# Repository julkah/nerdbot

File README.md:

# Bohlebots Nerdbot

This repository contains the last version of all files of the Nerdbot, a robot build in school with the team "Bohlebots" (bohlebots.de). It was built to participate at Robocup tournament in the 2v2 Soccer Open League. A documentation is enclosed as .pdf in German.

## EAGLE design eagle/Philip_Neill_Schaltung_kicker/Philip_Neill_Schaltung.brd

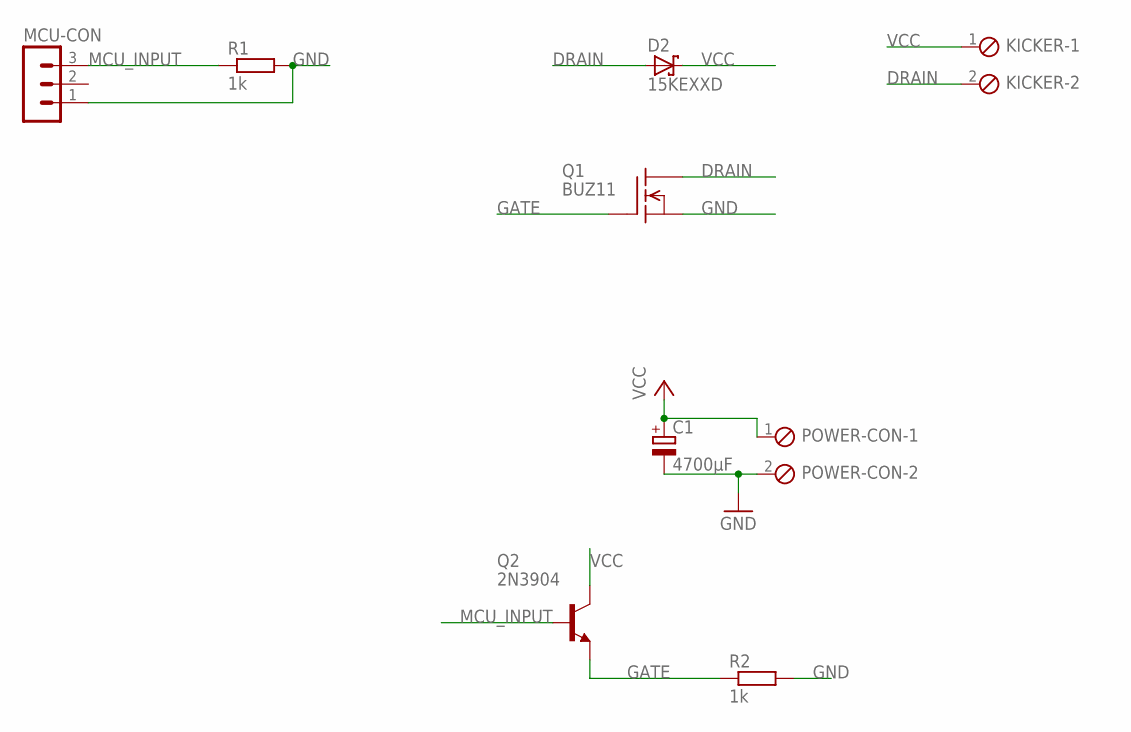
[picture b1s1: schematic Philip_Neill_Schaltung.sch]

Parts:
C1: 4700µF; EB20D
D2: 15KEXXD; DO201T15
KICKER: MPT2; 2POL254
MCU-CON: MA03-1
POWER-CON: MPT2; 2POL254
Q1: BUZ11; TO220
Q2: 2N3904; TO92
R1, R2: 1k; 0207/7

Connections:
DRAIN: D2.A, KICKER.2, Q1.2 (D)
GATE: Q1.1 (G), Q2.3 (E), R2.1
GND: C1.-, MCU-CON.1, POWER-CON.2, Q1.3 (S), R1.2, R2.2
MCU_INPUT: MCU-CON.3, Q2.2 (B), R1.1
VCC: C1.+, D2.C, KICKER.1, POWER-CON.1, Q2.1 (C)

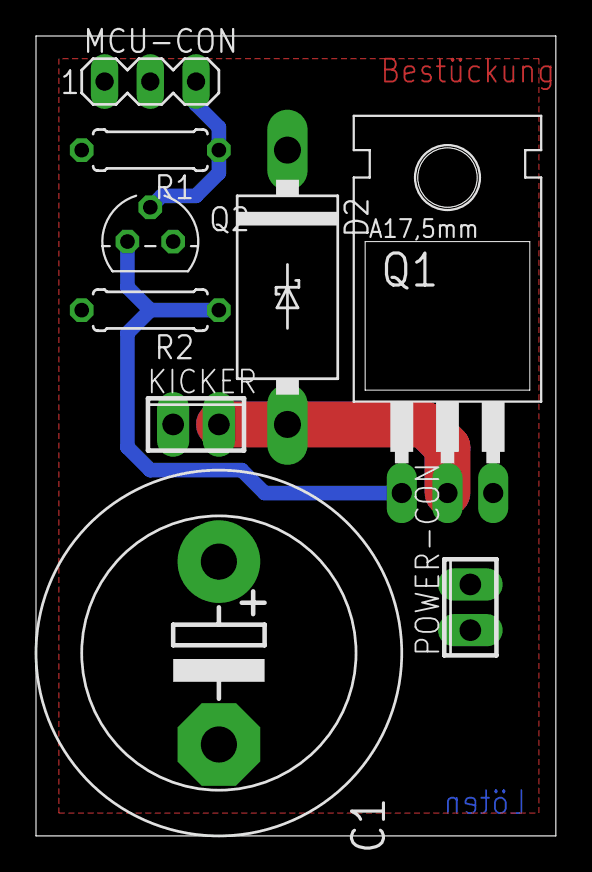
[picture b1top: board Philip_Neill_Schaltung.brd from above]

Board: 2 copper layers, 28.9 x 44.4 mm, 9 parts (0 on the bottom side), 5 nets.

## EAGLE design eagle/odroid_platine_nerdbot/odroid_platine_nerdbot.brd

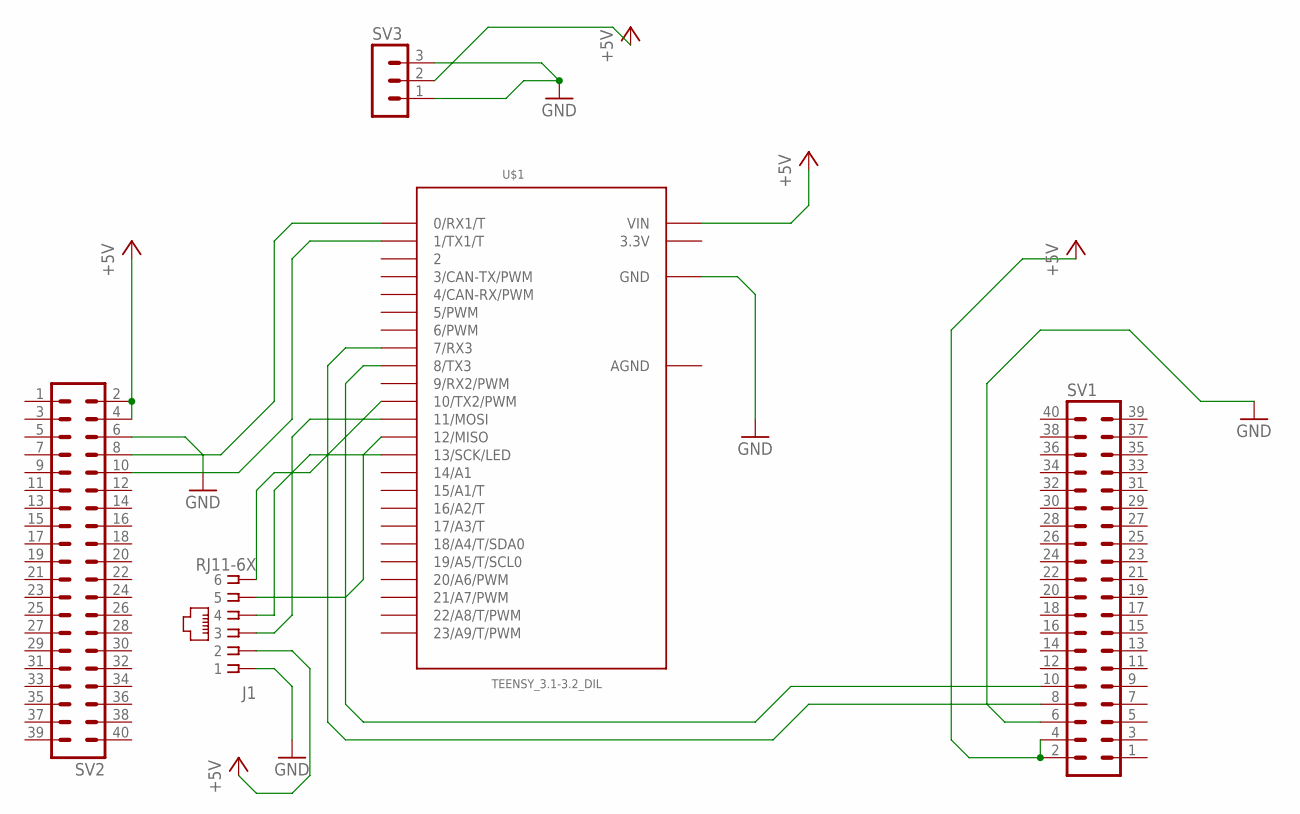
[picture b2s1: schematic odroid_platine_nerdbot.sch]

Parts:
J1: RJ11-6X; RJ11-NO_SHIELD
SV1, SV2: MA20-2
SV3: MA03-1
U$1: TEENSY_3.1-3.2_DIL; TEENSY_3.0-3.2&LC_DIL

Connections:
3.3V: U$1.3.3V
+5V: J1.2, SV1.2, SV1.4, SV2.2, SV2.4, SV3.2, U$1.VIN
AGND: U$1.AGND
GND: J1.1, SV1.6, SV2.6, SV3.1, SV3.3, U$1.GND
unnamed: SV2.8, U$1.0 (0/RX1/T)
unnamed: SV2.10, U$1.1 (1/TX1/T)
unnamed: SV1.8, U$1.7 (7/RX3)
unnamed: SV1.10, U$1.8 (8/TX3)
unnamed: J1.3, U$1.11 (11/MOSI)
unnamed: J1.4, U$1.13 (13/SCK/LED)
unnamed: J1.5, U$1.12 (12/MISO)
unnamed: J1.6, U$1.10 (10/TX2/PWM)

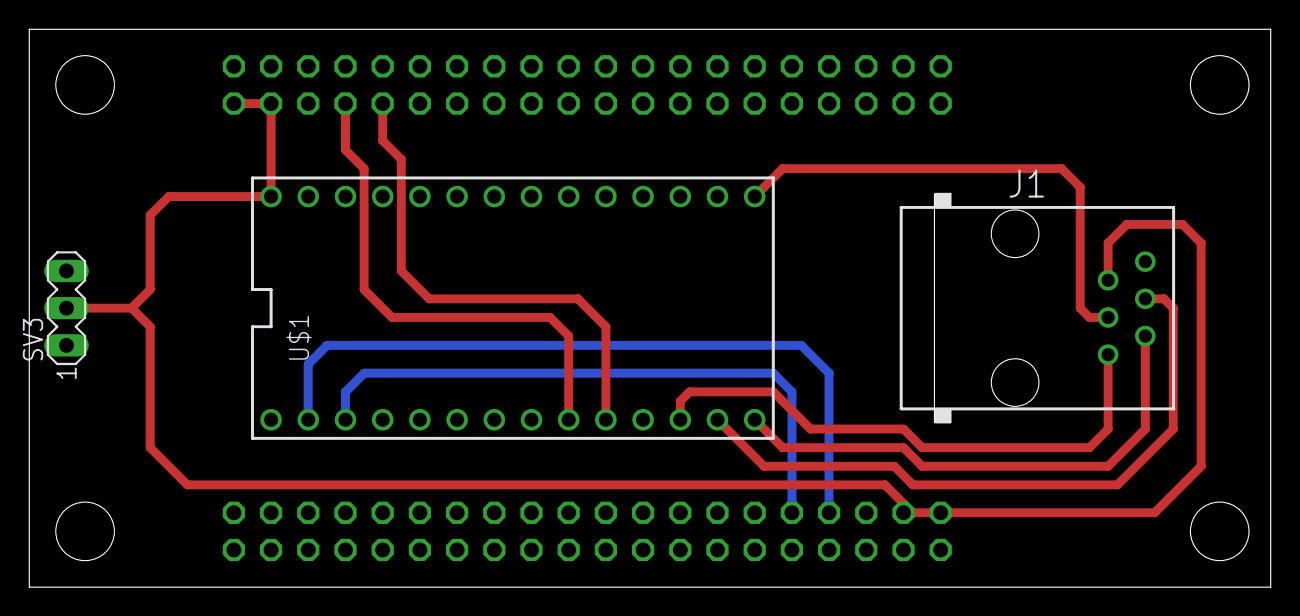
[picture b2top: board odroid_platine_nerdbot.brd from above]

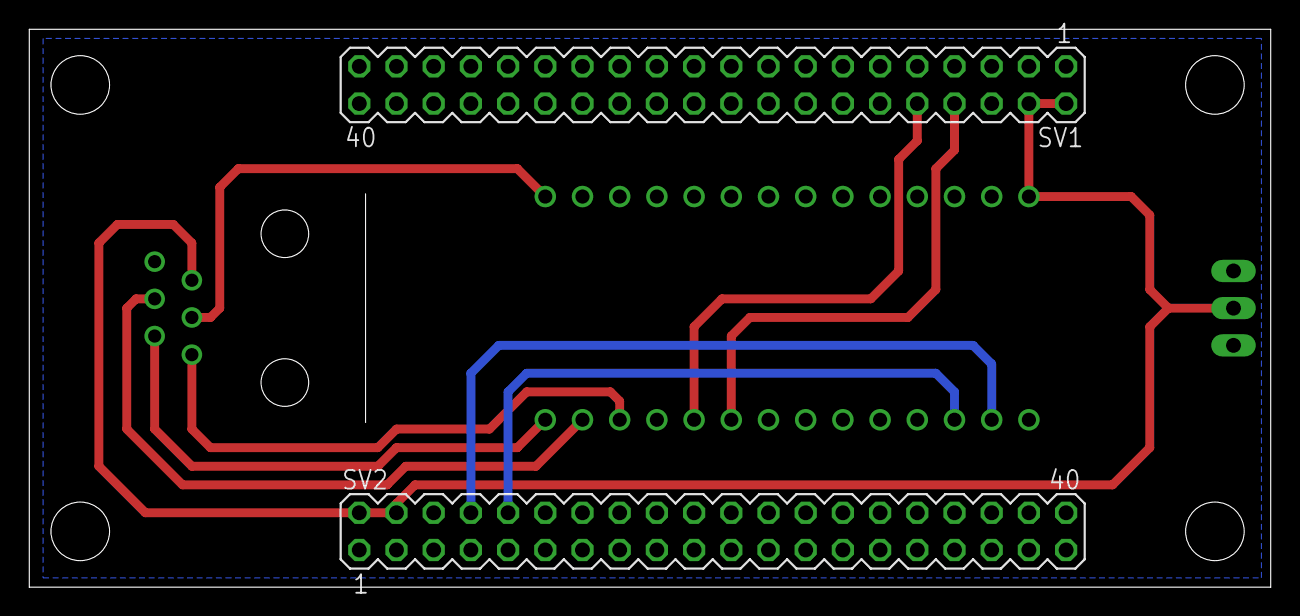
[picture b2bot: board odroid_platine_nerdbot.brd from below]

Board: 2 copper layers, 84.8 x 38.1 mm, 5 parts (2 on the bottom side), 10 nets.

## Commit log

2019-11-05 init repo
